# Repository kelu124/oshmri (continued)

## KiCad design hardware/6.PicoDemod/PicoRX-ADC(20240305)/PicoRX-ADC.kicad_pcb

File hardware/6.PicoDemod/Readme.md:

https://github.com/dawsonjon/PicoRX

dawsonjon wrote 12/11/2023 at 19:03
Hi, Thanks for your interest! I'm using a FST3253 for the mixer, and LTC6227 for the dual op-amp, but I used an LT6231 in the prototype and that worked fine. The PCB uses 74CBT3251 for the low-pass filter switching and a LTC6226 as an *optional* pre-amplifier. I have just uploaded the Schematic, Bill of Materials, and Gerbers.  The code (and loads more documentation) is on the github project https://github.com/dawsonjon/PicoRX and the wiki https://github.com/dawsonjon/PicoRX/wiki.  If anything is missing, or needs further explanation, please let me know. Thanks Jon

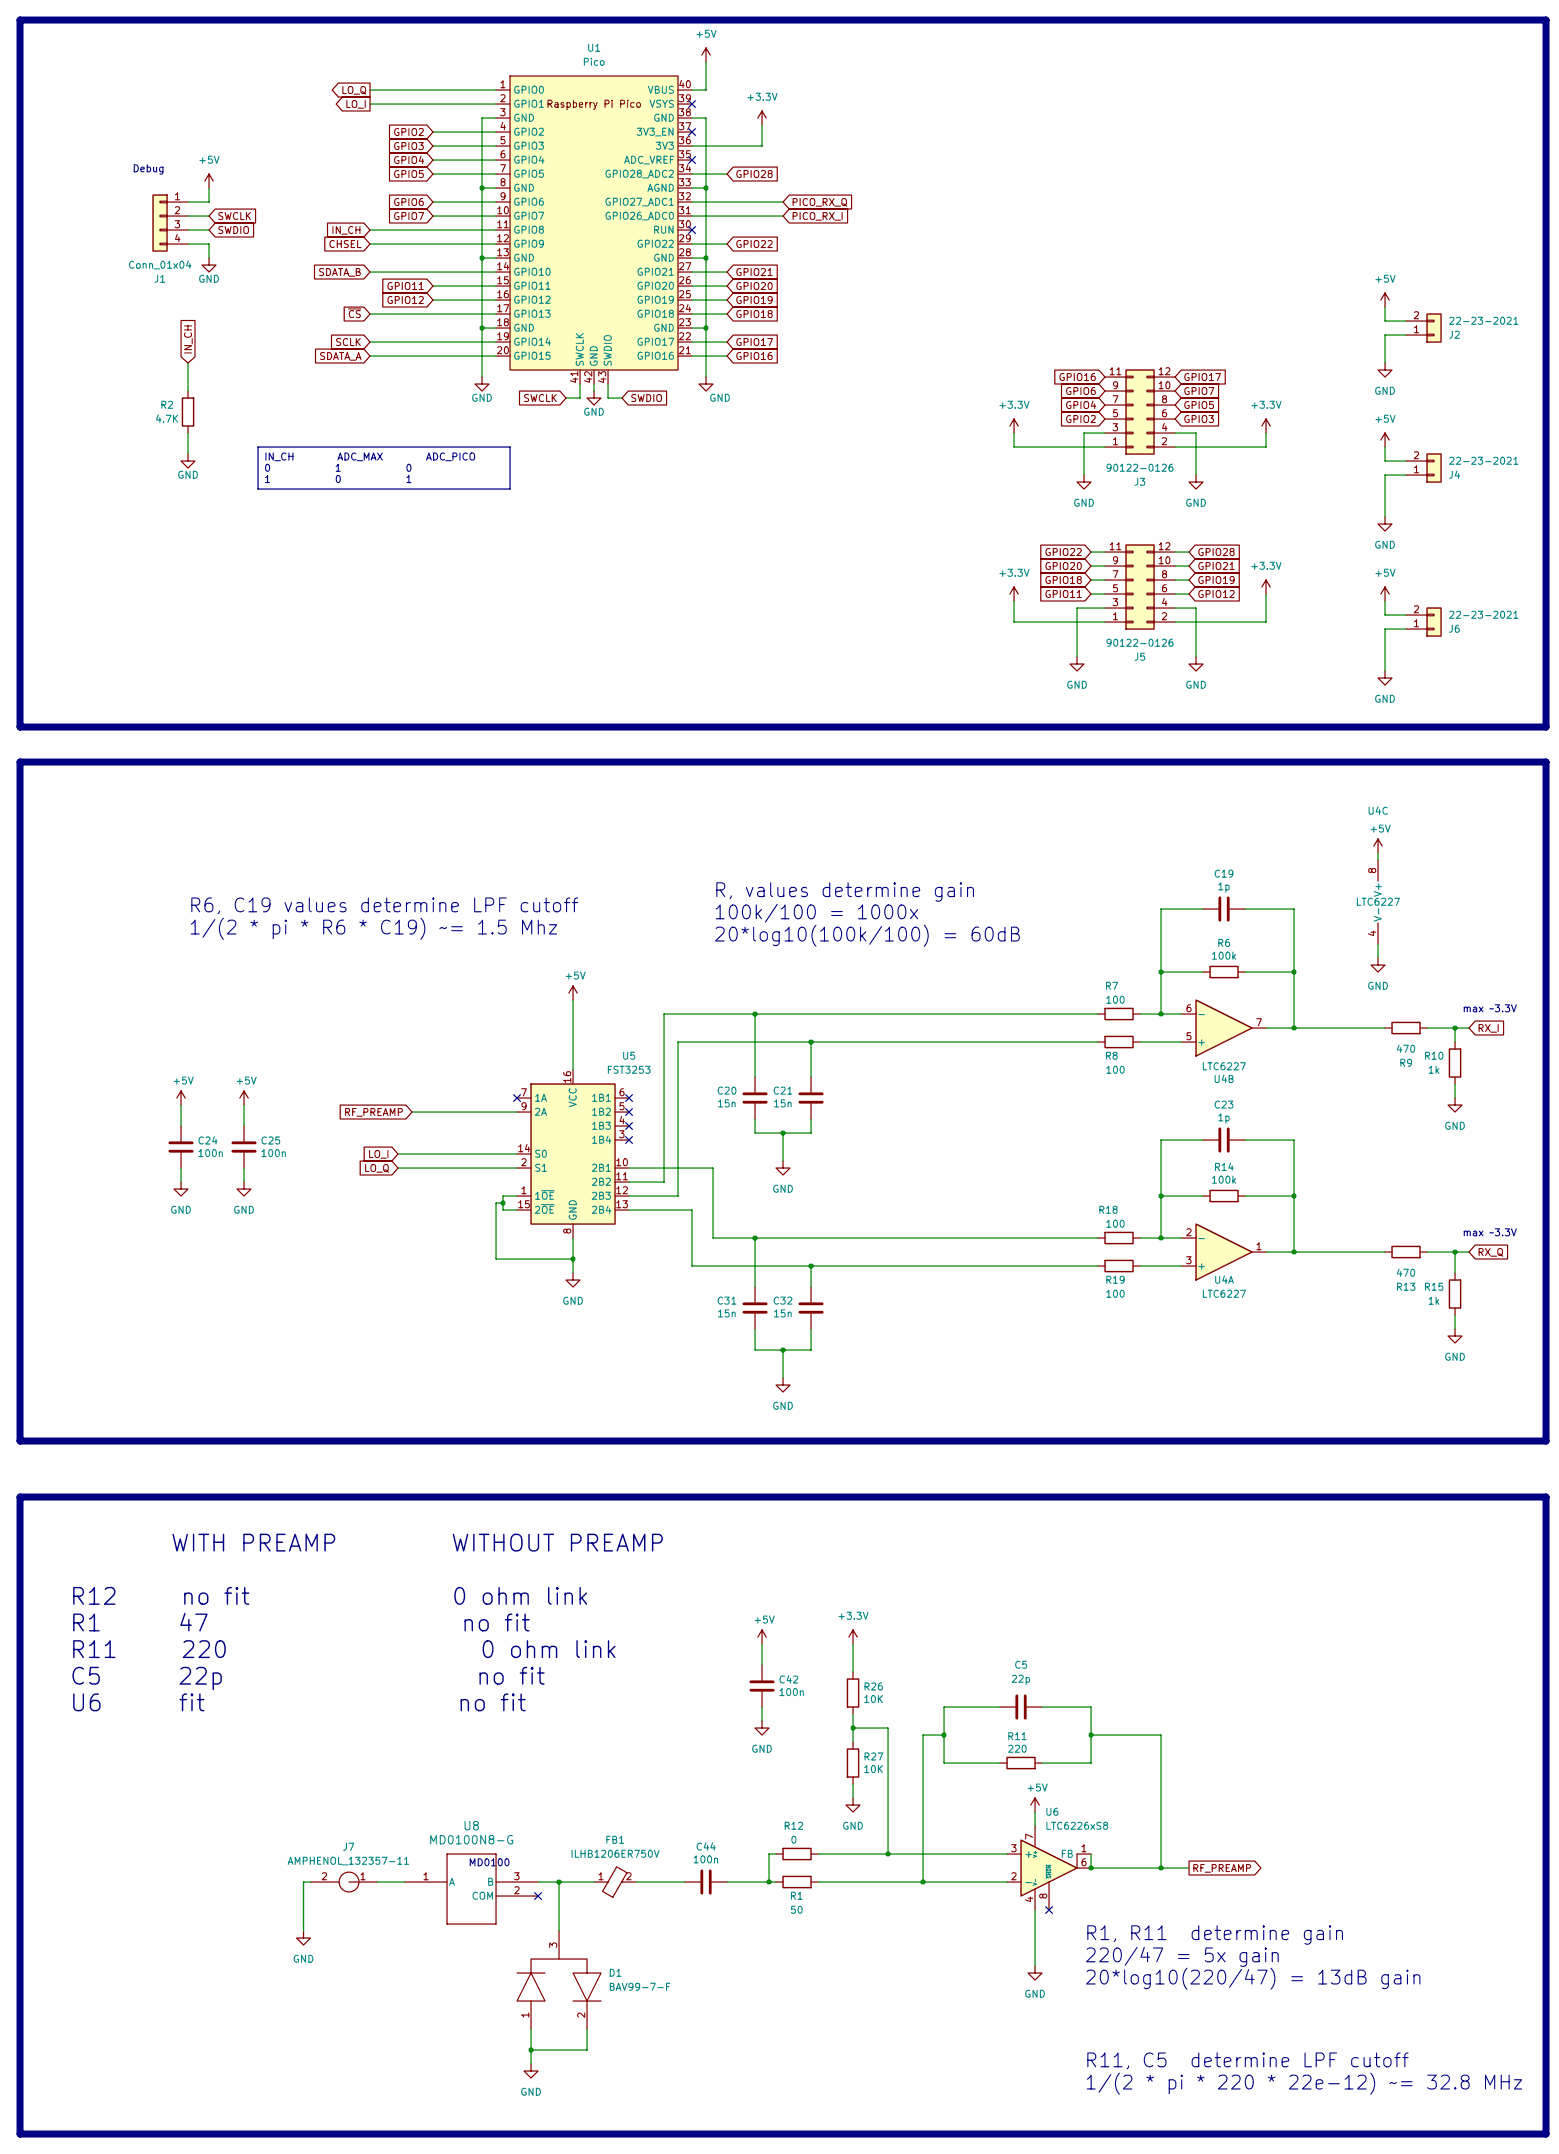
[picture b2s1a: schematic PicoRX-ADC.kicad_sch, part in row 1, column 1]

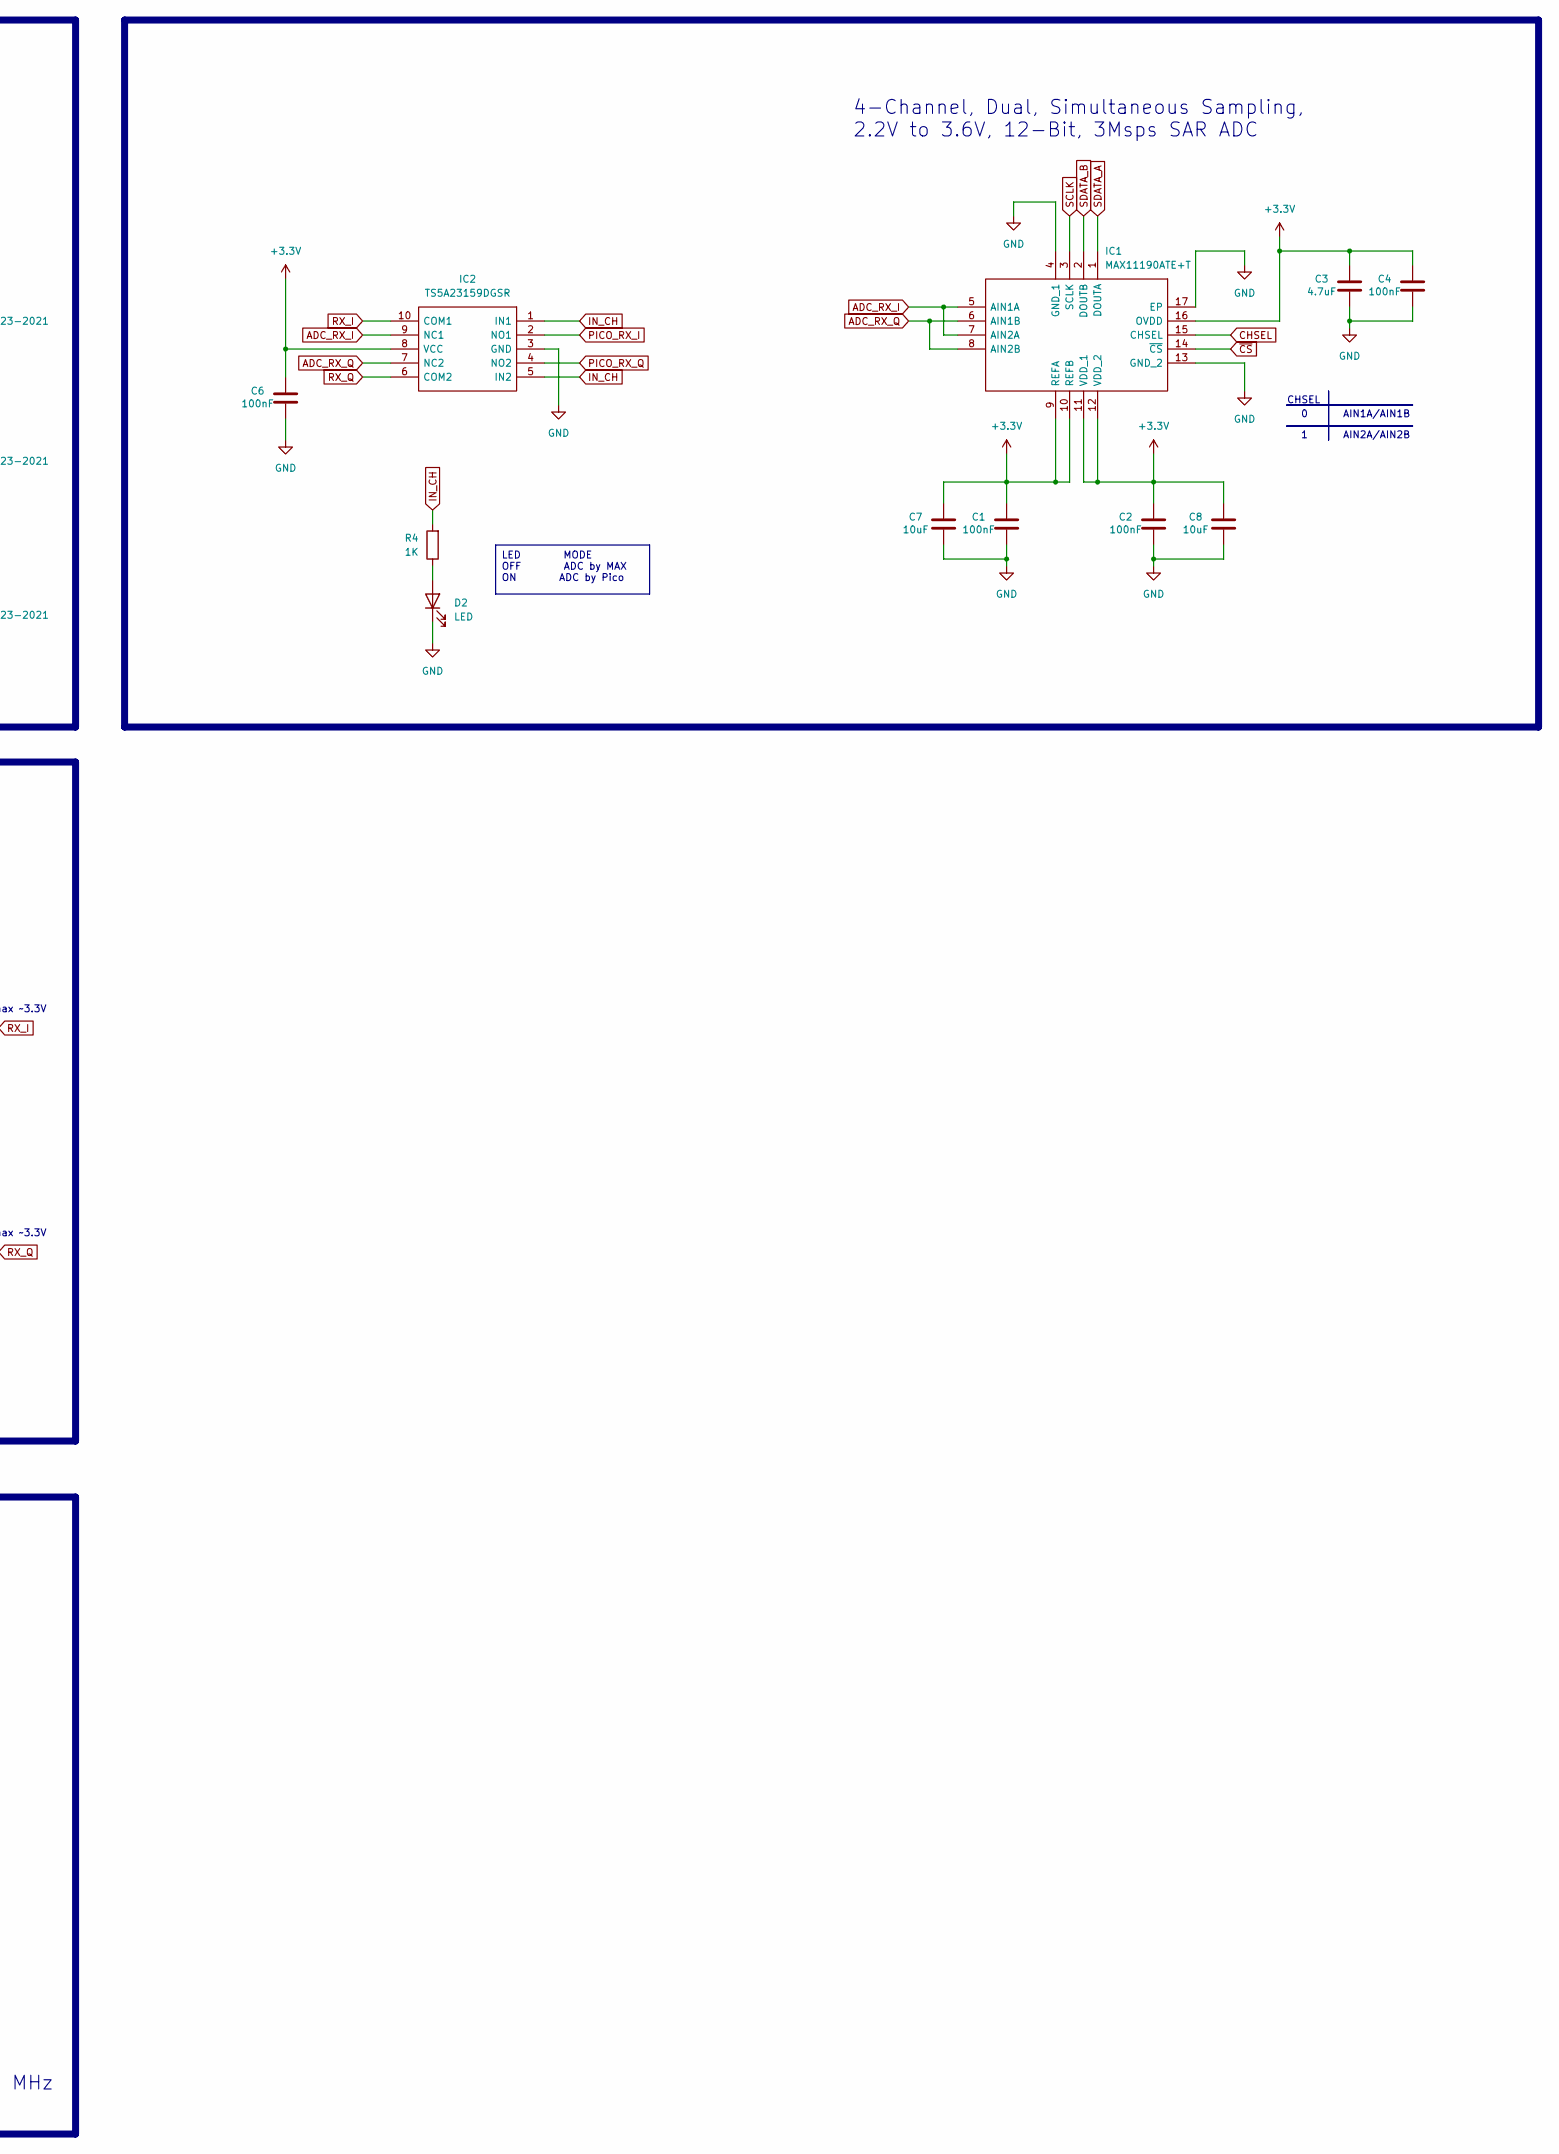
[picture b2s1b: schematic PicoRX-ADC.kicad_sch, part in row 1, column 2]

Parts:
C1, C2, C4, C6: 100nF; C_1206_3216Metric
C3: 4.7uF; C_1206_3216Metric
C5: 22p; C_1206_3216Metric
C7, C8: 10uF; C_1206_3216Metric
C19, C23: 1p; C_1206_3216Metric
C20, C21, C31, C32: 15n; C_1206_3216Metric
C24, C25, C42, C44: 100n; C_1206_3216Metric
D1: BAV99-7-F; SOT95P240X120-3N; Mouser Part Number 621-BAV99-F
D2: LED; LED_1206_3216Metric
FB1: ILHB1206ER750V; L_1206_3216Metric; Tolerance 25%; Mouser Part Number 81-BLM21B750S
IC1: MAX11190ATE+T; QFN50P300X300X80-17N; Mouser Part Number 700-MAX11190ATE+T
IC2: TS5A23159DGSR; SOP50P490X110-10N; Mouser Part Number 595-TS5A23159DGSR
J1: Conn_01x04; PinHeader_1x04_P2.54mm_Vertical
J2, J4, J6: 22-23-2021; PinHeader_1x02_P2.54mm_Vertical
J3, J5: 90122-0126; PinSocket_2x06_P2.54mm_Horizontal
J7: AMPHENOL_132357-11; Mouser Part Number 530-142-0701-801
R1: 50; R_1206_3216Metric
R2: 4.7K; R_1206_3216Metric
R4: 1K; R_1206_3216Metric
R6, R14: 100k; R_1206_3216Metric
R7, R8, R18, R19: 100; R_1206_3216Metric
R9, R13: 470; R_1206_3216Metric
R10, R15: 1k; R_1206_3216Metric
R11: 220; R_1206_3216Metric
R12: 0; R_1206_3216Metric
R26, R27: 10K; R_1206_3216Metric
U1: Pico; RPi_Pico_SMD
U4: LTC6227; MSOP-8-1EP_3x3mm_P0.65mm_EP1.68x1.88mm
U5: FST3253; SOIC-16_3.9x9.9mm_P1.27mm
U6: LTC6226xS8; SO-8_3.9x4.9mm_P1.27mm
U8: MD0100N8-G; SOT-89-3

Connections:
+3.3V: C1.2, C2.2, C3.2, C4.2, C6.2, C7.2, C8.2, IC1.9 (REFA), IC1.10 (REFB), IC1.11 (VDD_1), IC1.12 (VDD_2), IC1.16 (OVDD), IC2.8 (VCC), J3.1, J3.2, J5.1, J5.2, R26.1, U1.36 (3V3)
+5V: C24.1, C25.1, C42.1, J1.1, J2.2, J4.2, J6.2, U1.40 (VBUS), U4.8 (V+), U5.16 (VCC), U6.7 (V+)
ADC_RX_I: IC1.5 (AIN1A), IC1.7 (AIN2A), IC2.9 (NC1)
ADC_RX_Q: IC1.6 (AIN1B), IC1.8 (AIN2B), IC2.7 (NC2)
CHSEL: IC1.15 (CHSEL), U1.12 (GPIO9)
GND: C1.1, C2.1, C3.1, C4.1, C6.1, C7.1, C8.1, C20.1, C21.1, C24.2, C25.2, C31.1, C32.1, C42.2, D1.1, D1.2, D2.1 (K), IC1.4 (GND_1), IC1.13 (GND_2), IC1.17 (EP), IC2.3 (GND), J1.4, J2.1, J3.3, J3.4, J4.1, J5.3, J5.4, J6.1, J7.2, R2.1, R10.1, R15.1, R27.2, U1.3 (GND), U1.8 (GND), U1.13 (GND), U1.18 (GND), U1.23 (GND), U1.28 (GND), U1.33 (AGND), U1.38 (GND), U1.42 (GND), U4.4 (V-), U4.9, U5.1 (1~OE), U5.8 (GND), U5.15 (2~OE), U6.4 (V-), U6.5 (V-)
GPIO2: J3.5, U1.4 (GPIO2)
GPIO3: J3.6, U1.5 (GPIO3)
GPIO4: J3.7, U1.6 (GPIO4)
GPIO5: J3.8, U1.7 (GPIO5)
GPIO6: J3.9, U1.9 (GPIO6)
GPIO7: J3.10, U1.10 (GPIO7)
GPIO11: J5.5, U1.15 (GPIO11)
GPIO12: J5.6, U1.16 (GPIO12)
GPIO16: J3.11, U1.21 (GPIO16)
GPIO17: J3.12, U1.22 (GPIO17)
GPIO18: J5.7, U1.24 (GPIO18)
GPIO19: J5.8, U1.25 (GPIO19)
GPIO20: J5.9, U1.26 (GPIO20)
GPIO21: J5.10, U1.27 (GPIO21)
GPIO22: J5.11, U1.29 (GPIO22)
GPIO28: J5.12, U1.34 (GPIO28_ADC2)
IN_CH: IC2.1 (IN1), IC2.5 (IN2), R2.2, R4.2, U1.11 (GPIO8)
LO_I: U1.2 (GPIO1), U5.14 (S0)
LO_Q: U1.1 (GPIO0), U5.2 (S1)
unnamed: C19.2, R6.2, R9.1, U4.7
unnamed: C23.2, R13.1, R14.2, U4.1
unnamed: C44.1, R1.1, R12.2
unnamed: C44.2, FB1.2
unnamed: D2.2 (A), R4.1
unnamed: R19.1, U4.3 (+)
unnamed: C23.1, R14.1, R18.1, U4.2 (-)
unnamed: R8.1, U4.5 (+)
unnamed: C19.1, R6.1, R7.1, U4.6 (-)
unnamed: C31.2, R18.2, U5.10 (2B1)
unnamed: C20.2, R7.2, U5.11 (2B2)
unnamed: C21.2, R8.2, U5.12 (2B3)
unnamed: C32.2, R19.2, U5.13 (2B4)
unnamed: R12.1, R26.2, R27.1, U6.3 (+)
unnamed: C5.1, R1.2, R11.1, U6.2 (-)
unnamed: J7.1, U8.1 (A)
unnamed: D1.3, FB1.1, U8.3 (B)
PICO_RX_I: IC2.2 (NO1), U1.31 (GPIO26_ADC0)
PICO_RX_Q: IC2.4 (NO2), U1.32 (GPIO27_ADC1)
RF_PREAMP: C5.2, R11.2, U5.9 (2A), U6.1 (FB), U6.6
RX_I: IC2.10 (COM1), R9.2, R10.2
RX_Q: IC2.6 (COM2), R13.2, R15.2
SCLK: IC1.3 (SCLK), U1.19 (GPIO14)
SDATA_A: IC1.1 (DOUTA), U1.20 (GPIO15)
SDATA_B: IC1.2 (DOUTB), U1.14 (GPIO10)
SWCLK: J1.2, U1.41 (SWCLK)
SWDIO: J1.3, U1.43 (SWDIO)
~CS: IC1.14 (~CS), U1.17 (GPIO13)

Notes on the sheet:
IN_CH ADC_MAX ADC_PICO 0 1 0 1 0 1
LED MODE OFF ADC by MAX ON ADC by Pico
WITH PREAMP WITHOUT PREAMP R12 no fit 0 ohm link R1 47 no fit R11 220 0 ohm link C5 22p no fit U6 fit no fit
R6, C19 values determine LPF cutoff 1/(2 * pi * R6 * C19) ~= 1.5 Mhz
R11, C5 determine LPF cutoff 1/(2 * pi * 220 * 22e-12) ~= 32.8 MHz
4-Channel, Dual, Simultaneous Sampling, 2.2V to 3.6V, 12-Bit, 3Msps SAR ADC
MD0100
AIN1A/AIN1B
AIN2A/AIN2B
max ~3.3V
R, values determine gain 100k/100 = 1000x 20*log10(100k/100) = 60dB
CHSEL
R1, R11 determine gain 220/47 = 5x gain 20*log10(220/47) = 13dB gain
Debug

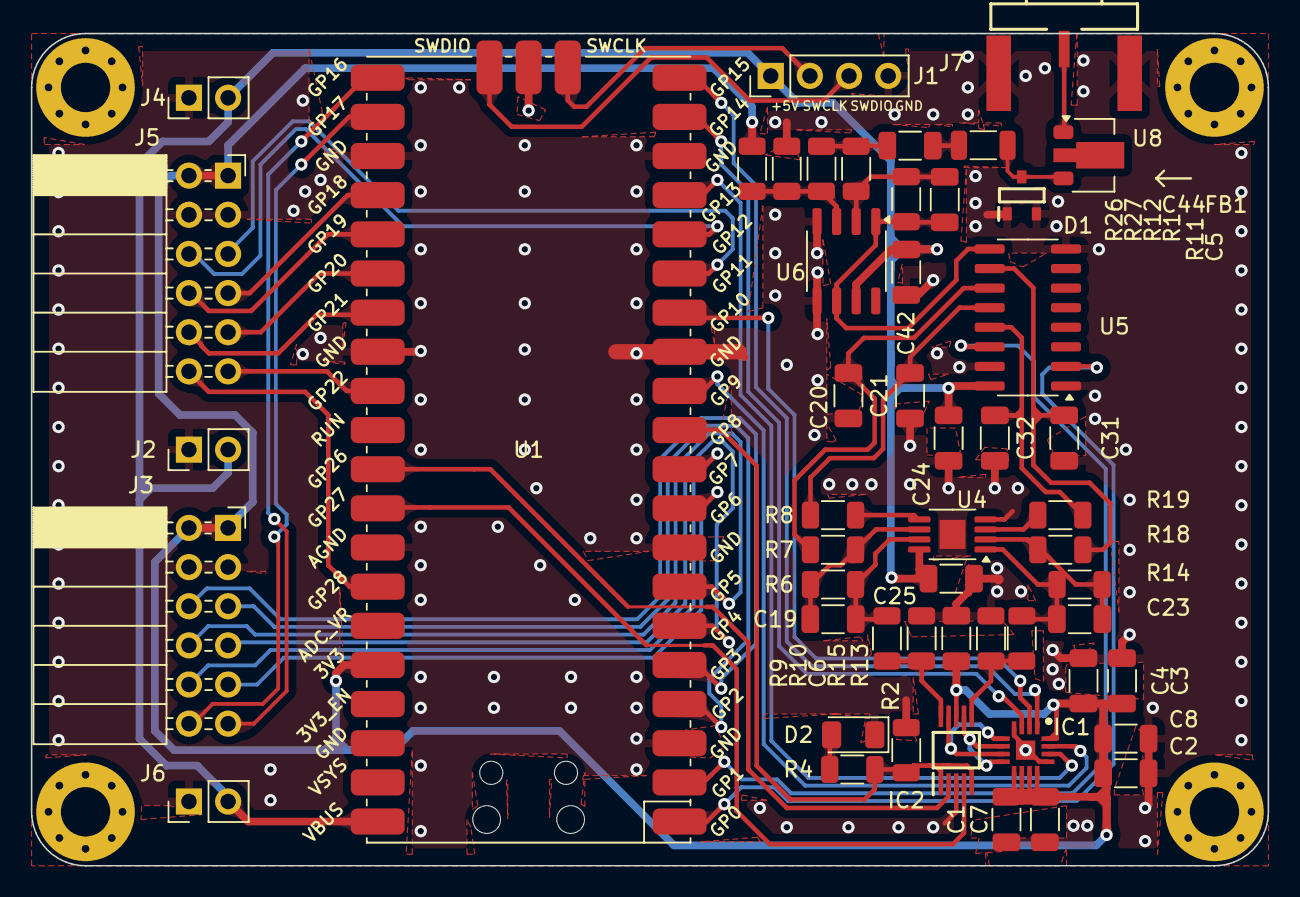
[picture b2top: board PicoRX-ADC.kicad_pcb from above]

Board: 2 copper layers, 80.2 x 54.0 mm, 52 parts (0 on the bottom side), 53 nets.

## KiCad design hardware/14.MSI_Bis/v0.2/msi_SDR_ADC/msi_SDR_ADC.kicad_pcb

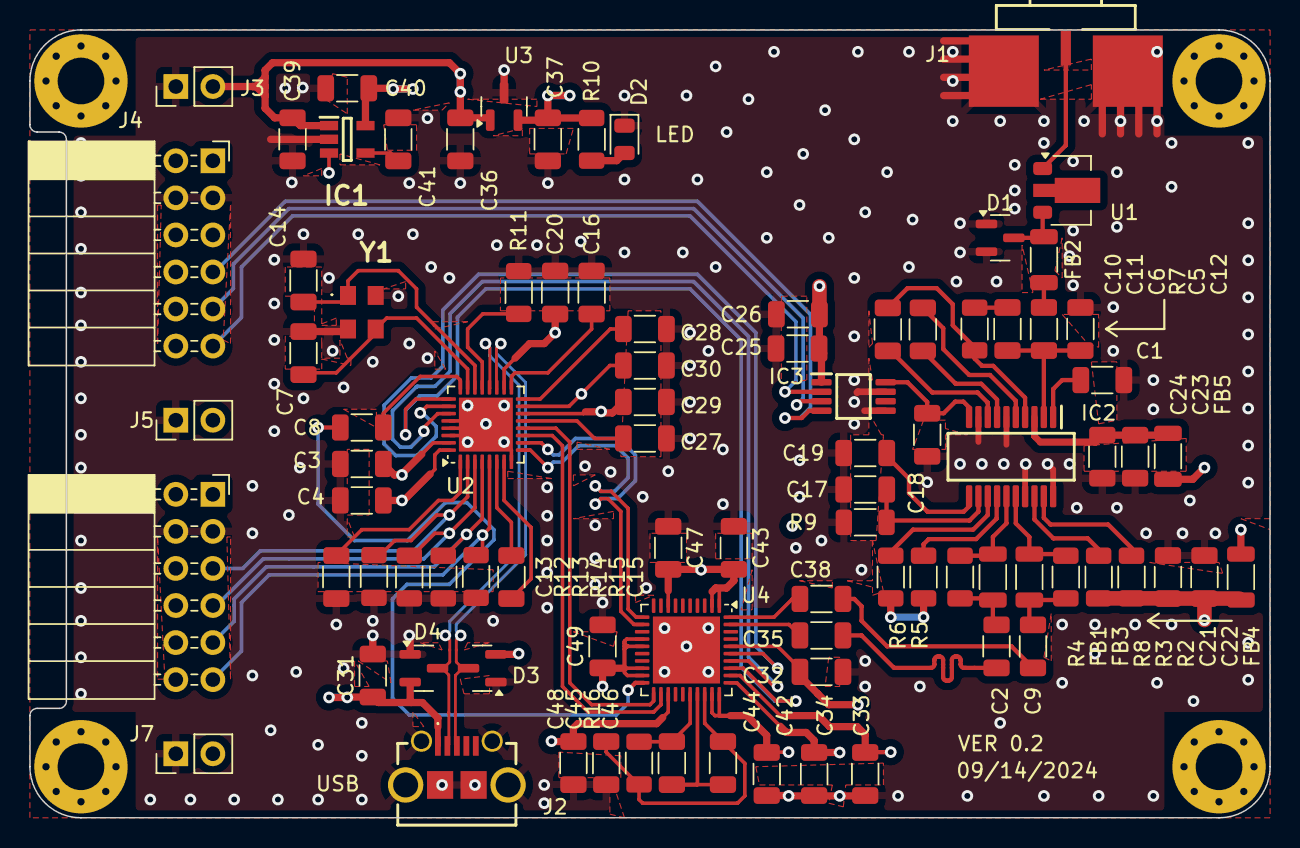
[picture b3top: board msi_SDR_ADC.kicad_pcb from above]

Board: 4 copper layers, 85.0 x 54.0 mm, 88 parts (0 on the bottom side), 66 nets.

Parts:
C1, C2, C5, C9, C10, C11, C17, C19, C22, C24, C26, C35, C38: 100nF; C_1206_3216Metric
C3, C4, C20, C25, C27, C29, C31, C33, C34, C36, C37, C39, C40: 10uF; C_1206_3216Metric
C6: 18nF; C_1206_3216Metric
C7, C14: 18pF; C_1206_3216Metric
C8, C15, C42, C43, C45, C47, C48, C49: 10nF; C_1206_3216Metric
C12: 22pF; C_1206_3216Metric
C13, C16, C28, C30, C32: 1uF; C_1206_3216Metric
C18, C21, C23: 1nF; C_1206_3216Metric
C41: 22nF; C_1206_3216Metric
C44: 6800pF; C_1206_3216Metric
C46: 33nF; C_1206_3216Metric
D1, D3, D4: BAV99; SOT-23
D2: LED; LED_0805_2012Metric
FB1, FB2, FB3, FB4, FB5: ILHB1206ER750V; L_1206_3216Metric
IC1: RT9193-18GB; SOT94P279X130-5N
IC2: AD8331ARQZ; SOP64P600X175-20N
IC3: MCP4812-E_MS; MCP4812-EMS
J1: AMPHENOL_132357-11; AMPHENOL_132357-11_EXT
J2: ZX62D-B-5PA8(30); ZX62DB5PA830
J3, J5, J7: 22-23-2021; PinHeader_1x02_P2.54mm_Vertical
J4, J6: 90122-0126; PinSocket_2x06_P2.54mm_Horizontal
R2, R3, R5, R6, R12, R13, R14, R15: 10K; R_1206_3216Metric
R4, R8: 100R; R_1206_3216Metric
R7: 280R; R_1206_3216Metric
R9: 12K; R_1206_3216Metric
R10, R11: 510R; R_1206_3216Metric
R16: 390R; R_1206_3216Metric
U1: MD0100N8-G; SOT-89-3
U2: msi2500; QFN-32-1EP_5x5mm_P0.5mm_EP3.7x3.7mm
U3: AP7313-30SAG; SOT-23
U4: msi001; QFN-40-1EP_6x6mm_P0.5mm_EP4.6x4.6mm
Y1: Crystal_GND24; ECS2401833BCHNTR3

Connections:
5VLNA: C23.1, C24.1, FB5.2, IC2.3 (VPSL)
5VVGA: C21.1, C22.1, FB4.1, R2.1, R3.1, R5.1, R6.1
+3.3V: J4.1, J4.2, J6.1, J6.2
+5V: C31.1, C36.1, C39.1, D3.2 (A), D4.2 (A), FB4.2, FB5.1, IC1.1 (VIN), J2.1 (VBUS), J3.2, J5.2, J7.2, U3.1 (Vin)
/I_IN_N: U2.10 (IIN_N), U4.12 (OPIB)
/I_IN_P: U2.9 (IIN_P), U4.11 (OPI)
/Q_IN_N: U2.12 (QIN_N), U4.21 (OPQB)
/Q_IN_P: U2.11 (QIN_P), U4.22 (OPQ)
/REFCLK: C8.1, U4.20 (REF-CLK)
DAC_G: C18.1, IC2.10 (GAIN), IC3.8 (VOUTA)
GND: C1.1, C3.2, C4.2, C7.1, C12.2, C13.1, C14.1, C16.2, C17.2, C18.2, C19.2, C20.2, C21.2, C22.2, C23.2, C24.2, C25.2, C26.2, C27.2, C28.2, C29.2, C30.2, C31.2, C32.1, C33.1, C34.1, C36.2, C37.2, C39.2, C40.2, C41.2, C42.1, C43.1, C45.2, C47.1, C48.2, C49.2, D1.1 (K), D1.2 (A), D2.1 (K), D3.1 (K), D4.1 (K), IC1.2 (GND), IC2.6 (COML), IC2.9 (MODE), IC2.17 (COMM_1), IC2.20 (COMM_2), IC3.5 (~LDAC), IC3.7 (VSS), J1.2, J2.5 (GND), J2.6 (Shield), J3.1, J4.3, J4.4, J5.1, J6.3, J6.4, J7.1, R9.2, R11.1, R12.2, R13.2, R14.2, R15.2, U2.8 (VEE_ADC), U2.28 (XTAL_SEL), U2.29 (TEST1), U2.30 (TEST2), U2.33 (GND), U3.3 (GND), U4.41 (GND), Y1.2, Y1.4
GPIO_0: J6.5, R12.1, U2.2 (GPIO_0)
GPIO_1: J6.7, R13.1, U2.3 (GPIO_1)
GPIO_2: J6.9, R14.1, U2.4 (GPIO_2)
GPIO_3: J6.11, R15.1, U2.5 (GPIO_3)
unnamed: C2.1, FB1.2, R4.2
unnamed: C5.1, FB2.2
unnamed: C6.2, R7.1
unnamed: C9.1, FB3.2, R8.2
unnamed: D2.2 (A), R10.2
unnamed: C41.1, IC1.4 (BP)
unnamed: IC2.19 (ENBL), R2.2
unnamed: IC2.18 (ENBV), R3.2
unnamed: IC2.13 (HILO), R6.2
unnamed: C5.2, C6.1, C12.1, IC2.2 (INH)
unnamed: C1.2, IC2.1 (LMD)
unnamed: C10.1, IC2.4 (LON), R7.2
unnamed: C11.1, IC2.5 (LOP)
unnamed: C17.1, IC2.12 (RCLMP), R9.1
unnamed: C19.1, IC2.11 (VCM)
unnamed: C10.2, IC2.8 (VIN)
unnamed: C11.2, IC2.7 (VIP)
unnamed: IC2.14 (VPOS), R5.2
unnamed: J1.1, U1.1 (A)
unnamed: D1.3 (K), FB2.1, U1.3 (B)
unnamed: C15.2, U2.7 (ADC_REF_N)
unnamed: C15.1, U2.6 (ADC_REF_P)
unnamed: C8.2, U2.24 (REFOUT)
unnamed: R11.2, U2.21 (REST)
unnamed: C16.1, U2.17 (V15_VCO)
unnamed: C27.1, U2.13 (V18_ADC)
unnamed: C28.1, U2.16 (V18_PHY)
unnamed: C13.2, U2.1 (VCC_GPIO)
unnamed: C14.2, U2.22 (X0), Y1.1
unnamed: C7.2, U2.23 (X1), Y1.3
unnamed: C38.2, U4.40 (AMP2_IN)
unnamed: C35.2, U4.39 (AMP2_INB)
unnamed: C44.1, C46.1, U4.27 (CP-OUT)
unnamed: C46.2, R16.2, U4.26 (LFILT-PC)
unnamed: C44.2, C45.1, R16.1, U4.28 (VCO-VCC)
SCK: IC3.3 (SCK), J4.9
SDI: IC3.4 (SDI), J4.7
SPI_CLK: J6.10, U2.27 (SPI_CLK), U4.34 (CLK)
SPI_DATA: J6.6, U2.26 (SPI_DAT), U4.35 (DATA)
SPI_LAT: J6.8, U2.25 (SPI_LAT), U4.33 (EN)
TO_ADC_H: C2.2, C35.1
TO_ADC_L: C9.2, C38.1
USB_N: D4.3 (K), J2.2 (D-), U2.20 (DM)
USB_P: D3.3 (K), J2.3 (D+), U2.19 (DP)
V18-SYNTH: C30.1, IC1.3 (EN), U2.15 (V18_SYNTH)
VDDI: C3.1, C34.2, U2.31 (V18_DIGITAL), U4.31 (VDDI)
VDIG: C4.1, C20.1, C25.1, C26.1, C29.1, C37.1, IC3.1 (VDD), R10.1, U2.14 (VCC_3V_PM), U2.18 (VCC_3V_XCVR), U2.32 (VCC_3V_DIGITAL), U3.2 (Vout)
VOH: FB1.1, IC2.15 (VOH), R4.1
VOL: FB3.1, IC2.16 (VOL), R8.1
VRF: C32.2, C33.2, C40.1, C42.2, C43.2, C47.2, C48.1, C49.1, IC1.5 (VOUT), U4.1 (VCC1), U4.2 (VCC2), U4.8 (VCC3), U4.14 (VCC5), U4.15 (VCC6), U4.18 (VCC7), U4.19 (VCC8), U4.23 (VCC9), U4.29 (VCC10), U4.30 (VCC11), U4.32 (VDD), U4.36 (VCC12)
~CS: IC3.2 (~CS), J4.11

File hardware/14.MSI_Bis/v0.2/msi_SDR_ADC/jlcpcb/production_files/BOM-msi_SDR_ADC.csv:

Comment,Designator,Footprint,LCSC
1uF,C13,C_1206_3216Metric,
100nF,C9,C_1206_3216Metric,
10uF,C29,C_1206_3216Metric,
10nF,C45,C_1206_3216Metric,
1nF,C21,C_1206_3216Metric,
90122-0126,J4,PinSocket_2x06_P2.54mm_Horizontal,
10uF,C27,C_1206_3216Metric,
100nF,C26,C_1206_3216Metric,
10uF,C25,C_1206_3216Metric,
AD8331ARQZ,IC2,SOP64P600X175-20N,
10uF,C3,C_1206_3216Metric,
280R,R7,R_1206_3216Metric,
18pF,C7,C_1206_3216Metric,
10uF,C40,C_1206_3216Metric,
22-23-2021,J3,PinHeader_1x02_P2.54mm_Vertical,
10nF,C47,C_1206_3216Metric,
10uF,C34,C_1206_3216Metric,
10nF,C15,C_1206_3216Metric,
BAV99,D4,SOT-23,
100nF,C35,C_1206_3216Metric,
msi001,U4,QFN-40-1EP_6x6mm_P0.5mm_EP4.6x4.6mm,
390R,R16,R_1206_3216Metric,
10K,R3,R_1206_3216Metric,
ILHB1206ER750V,FB4,L_1206_3216Metric,
BAV99,D1,SOT-23,
10uF,C20,C_1206_3216Metric,
ILHB1206ER750V,FB5,L_1206_3216Metric,
10nF,C8,C_1206_3216Metric,
90122-0126,J6,PinSocket_2x06_P2.54mm_Horizontal,
ZX62D-B-5PA8(30),J2,ZX62DB5PA830,
AP7313-30SAG,U3,SOT-23,
12K,R9,R_1206_3216Metric,
10nF,C48,C_1206_3216Metric,
LED,D2,LED_0805_2012Metric,
ILHB1206ER750V,FB3,L_1206_3216Metric,
10uF,C37,C_1206_3216Metric,
10uF,C39,C_1206_3216Metric,
10uF,C4,C_1206_3216Metric,
BAV99,D3,SOT-23,
22-23-2021,J7,PinHeader_1x02_P2.54mm_Vertical,
ILHB1206ER750V,FB1,L_1206_3216Metric,
1nF,C23,C_1206_3216Metric,
10uF,C36,C_1206_3216Metric,
10uF,C31,C_1206_3216Metric,
10K,R12,R_1206_3216Metric,
100nF,C17,C_1206_3216Metric,
MCP4812-E_MS,IC3,MCP4812-EMS,
10K,R15,R_1206_3216Metric,
100nF,C10,C_1206_3216Metric,
100nF,C5,C_1206_3216Metric,
RT9193-18GB,IC1,SOT94P279X130-5N,
Crystal_GND24,Y1,ECS2401833BCHNTR3,
100nF,C11,C_1206_3216Metric,
AMPHENOL_132357-11,J1,AMPHENOL_132357-11_EXT,
18nF,C6,C_1206_3216Metric,
MD0100N8-G,U1,SOT-89-3,
100nF,C22,C_1206_3216Metric,
100nF,C24,C_1206_3216Metric,
33nF,C46,C_1206_3216Metric,
ILHB1206ER750V,FB2,L_1206_3216Metric,
22pF,C12,C_1206_3216Metric,
1uF,C28,C_1206_3216Metric,
10K,R5,R_1206_3216Metric,
510R,R10,R_1206_3216Metric,
1nF,C18,C_1206_3216Metric,
1uF,C16,C_1206_3216Metric,
1uF,C30,C_1206_3216Metric,
100nF,C38,C_1206_3216Metric,
10nF,C49,C_1206_3216Metric,
10K,R6,R_1206_3216Metric,
10K,R14,R_1206_3216Metric,
100R,R4,R_1206_3216Metric,
22nF,C41,C_1206_3216Metric,
100R,R8,R_1206_3216Metric,
msi2500,U2,QFN-32-1EP_5x5mm_P0.5mm_EP3.7x3.7mm,
10nF,C42,C_1206_3216Metric,
22-23-2021,J5,PinHeader_1x02_P2.54mm_Vertical,
1uF,C32,C_1206_3216Metric,
100nF,C19,C_1206_3216Metric,
18pF,C14,C_1206_3216Metric,
10nF,C43,C_1206_3216Metric,
510R,R11,R_1206_3216Metric,
100nF,C2,C_1206_3216Metric,
10K,R2,R_1206_3216Metric,
10uF,C33,C_1206_3216Metric,
6800pF,C44,C_1206_3216Metric,
10K,R13,R_1206_3216Metric,
100nF,C1,C_1206_3216Metric,

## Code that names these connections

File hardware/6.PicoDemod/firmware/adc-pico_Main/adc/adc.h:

//!
//! \file       adc.h
//! \author     Abdelrahman Ali
//! \date       2024-04-28
//!
//! \brief      adc pio.
//!

#ifndef ADC_H
#define ADC_H

//---------------------------------------------------------------------------
// INCLUDES
//---------------------------------------------------------------------------

#include <stdio.h>
#include <stdlib.h>
#include "pico/stdlib.h"
#include "hardware/pio.h"
#include "hardware/adc.h"
#include "hardware/gpio.h"
#include "hardware/clocks.h"

//---------------------------------------------------------------------------
// CONSTANTS
//---------------------------------------------------------------------------

#define LO_Q 0
#define LO_I 1
#define SAMPLE_COUNT 400
#define LO_CLK 16000000

#define ADC0 26
#define ADC1 27

#define ADC_NUM0 0
#define ADC_NUM1 1

#define ADC_VREF 3.3
#define ADC_RANGE (1 << 12)
#define ADC_CONVERT (ADC_VREF / (ADC_RANGE - 1))

#define IN_CH 8
#define CHSEL 9
#define DOUTA 15
#define DOUTB 10
#define CS 13
#define SCLK 14

//---------------------------------------------------------------------------
// LO INIT FUNCTION
//---------------------------------------------------------------------------

void pio_lo_init();

//---------------------------------------------------------------------------
// PICO ADC INIT FUNCTION
//---------------------------------------------------------------------------
void pico_adc_init();

//---------------------------------------------------------------------------
// ADC MAX GPIO INIT FUNCTION
//---------------------------------------------------------------------------
void adc_max_gpio_init();

//---------------------------------------------------------------------------
// GPIO delays
//---------------------------------------------------------------------------
void delay_50ns();
void delay_250ns();

//---------------------------------------------------------------------------
// GET ADC0 FUNCTION
//---------------------------------------------------------------------------
void get_adc0(uint16_t i);

//---------------------------------------------------------------------------
// GET ADC1 FUNCTION
//---------------------------------------------------------------------------
void get_adc1(uint16_t i);

//---------------------------------------------------------------------------
// GET DOUTA FUNCTION
//---------------------------------------------------------------------------
void get_douta(uint16_t i);

//---------------------------------------------------------------------------
// GET DOUTB FUNCTION
//---------------------------------------------------------------------------
void get_doutb(uint16_t i);

//---------------------------------------------------------------------------
// ADC MAIN FUNCTION
//---------------------------------------------------------------------------

void adc();

//---------------------------------------------------------------------------
// END OF FILE
//---------------------------------------------------------------------------

#endif

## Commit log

2020-12-24 Initial ideas / specs
2020-12-24 pdfs update
2020-12-24 Melon
2020-12-24 Updated specs
2020-12-29 New articles
2021-01-14 Update of specs accding to Tom
2021-03-18 Raw data?
2022-01-15 RawData
2022-01-15 Cleaning
2022-01-15 Adding semi large files
2022-01-15 Adding readme
2022-01-15 Updating reconstruction from a 2D plane
2022-01-27 Further toying with data
2022-05-01 Hardware
2022-05-07 Adding specs
2022-05-21 new MSI chips
2022-06-05 Add doc pmods
2022-06-05 pulser
2022-06-18 Update pulser
2022-06-18 remove sdr
2022-07-31 New AFE
2022-11-27 Addign pulser
2022-12-20 New version of AFE
2023-02-11 Update of BOM and Schematics for main board
2023-03-12 Blinky working
2023-03-13 Tests with ECP5 and FT600
2023-03-24 USB v2
2023-03-24 read write
2023-03-25 Loop works
2023-03-26 New tests
2023-03-30 20230330
2023-04-02 add pic
2023-04-06 0406
2023-05-28 New tests with FT600
2023-05-28 New drawings
2023-05-28 New adc tests
2023-05-28 Test new pins
2023-06-25 Feasa for PICO3
2023-10-08 New images
2023-11-01 New MSI pusler
2023-11-11 New prod files
2024-01-23 Adding dmod stuff
2024-01-25 Adding pitch
2024-01-26 Design ADC
2024-01-27 New files
2024-02-19 New PMODs
2024-05-05 autoupdate
